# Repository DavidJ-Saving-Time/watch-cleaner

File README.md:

So this is a very rough draft of code designed to run on an esp32 to control a watch cleaning machine see this YouTube video https://youtu.be/Opr75n8DbYY I'll be adding to this and making it easier for people to use. Please feel free to pitch in

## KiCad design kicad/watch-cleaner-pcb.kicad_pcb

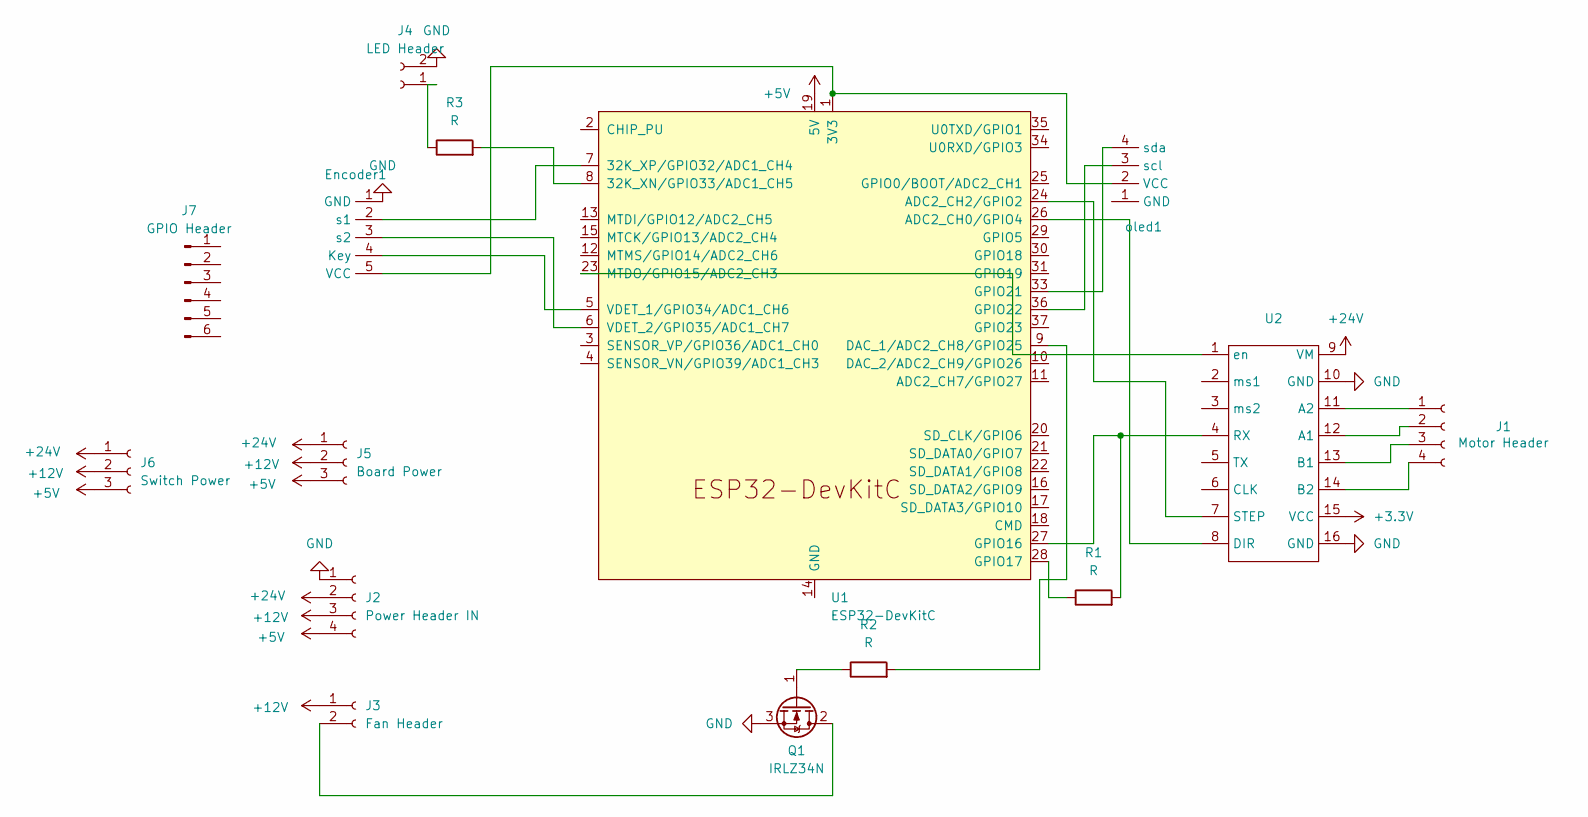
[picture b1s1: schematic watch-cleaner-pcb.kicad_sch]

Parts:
Encoder1: JST_EH_B5B-EH-A_1x05_P2.50mm_Vertical
J1: Motor Header; JST_EH_B4B-EH-A_1x04_P2.50mm_Vertical
J2: Power Header IN; JST_EH_S4B-EH_1x04_P2.50mm_Horizontal
J3: Fan Header; JST_EH_S2B-EH_1x02_P2.50mm_Horizontal
J4: LED Header; JST_EH_B2B-EH-A_1x02_P2.50mm_Vertical
J5: Board Power; JST_EH_B3B-EH-A_1x03_P2.50mm_Vertical
J6: Switch Power; JST_EH_B3B-EH-A_1x03_P2.50mm_Vertical
J7: GPIO Header; PinHeader_1x06_P2.54mm_Vertical
Q1: IRLZ34N; TO-220-3_Vertical
R1, R2, R3: R; R_Axial_DIN0207_L6.3mm_D2.5mm_P10.16mm_Horizontal
U1: ESP32-DevKitC
U2: MODULE_TMC2209_SILENTSTEPSTICK
oled1: JST_EH_B4B-EH-A_1x04_P2.50mm_Vertical

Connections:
+3.3V: U2.15 (VCC)
+5V: J2.4, J5.3, J6.3, U1.19 (5V)
+12V: J2.3, J3.1, J5.2, J6.2
+24V: J2.2, J5.1, J6.1, U2.9 (VM)
unnamed: Encoder1.4 (Key), U1.5 (VDET_1/GPIO34/ADC1_CH6)
unnamed: Encoder1.5 (VCC), U1.1 (3V3), oled1.2 (VCC)
unnamed: Encoder1.2 (s1), U1.7 (32K_XP/GPIO32/ADC1_CH4)
unnamed: Encoder1.3 (s2), U1.6 (VDET_2/GPIO35/ADC1_CH7)
unnamed: J1.1, U2.11 (A2)
unnamed: J1.2, U2.12 (A1)
unnamed: J1.3, U2.13 (B1)
unnamed: J1.4, U2.14 (B2)
unnamed: J3.2, Q1.2 (D)
unnamed: J4.1, R3.1
unnamed: Q1.1 (G), R2.1
unnamed: R3.2, U1.8 (32K_XN/GPIO33/ADC1_CH5)
unnamed: U1.26 (ADC2_CH0/GPIO4), U2.8 (DIR)
unnamed: U1.24 (ADC2_CH2/GPIO2), U2.7 (STEP)
unnamed: R2.2, U1.9 (DAC_1/ADC2_CH8/GPIO25)
unnamed: R1.2, U1.27 (GPIO16), U2.4 (RX)
unnamed: R1.1, U1.28 (GPIO17)
unnamed: U1.33 (GPIO21), oled1.4 (sda)
unnamed: U1.36 (GPIO22), oled1.3 (scl)
unnamed: U1.23 (MTDO/GPIO15/ADC2_CH3), U2.1 (en)

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
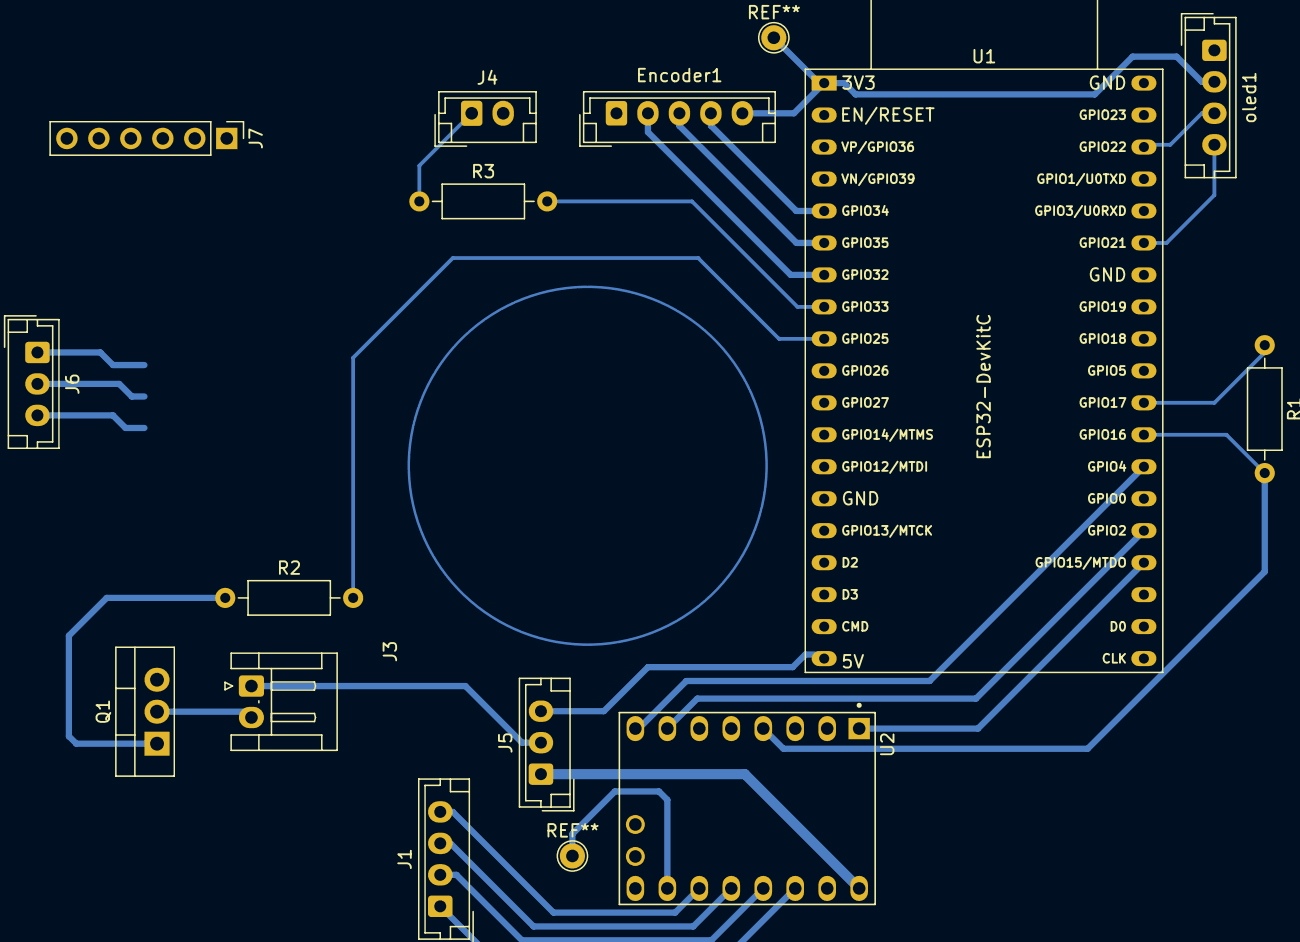
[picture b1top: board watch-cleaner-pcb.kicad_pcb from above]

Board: 2 copper layers, 14 parts (0 on the bottom side), 24 nets.

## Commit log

2024-11-28 Version 1.1 sort of it's a work in progress at this point.
    Added over the air updates
2024-11-28 5467a024b6a19
2024-11-28 Added kicad files
2024-11-28 Create LICENSE
